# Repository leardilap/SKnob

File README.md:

# SKnob
The safety knob for your stove

# Overall shape
- Two main PCBs with 24x17mm dimmentions joined with ~~flex PCB~~ 2 wires

# Battery
- CR1225 or similar with ~50mA could allow to be mounted in the top of one of the PCBs as the space is round in the middle
- Holder: Manufacturer Part Number 	BK-885-TR 

# Bluetooth-STM32
- Use the STM32WB55Cx chip 
- Workshop: https://www.youtube.com/watch?v=5Lp9cDBzG94&list=PLnMKNibPkDnGRfqUO1Q_-1nW-tOKfDQbc&index=1

# Antena
- Manufacturer 	PulseLarsen Antennas
Manufacturer Part Number 	W3008 

# Similar product
- https://burneralert.com/

# Commercial
- Don't be a SKnob, do you mean our safety knobs for our burnner?. this is how I protect my family everyday, no more sleepless nights, waking up at night just to check the stove. With SKnob I feel safe. Don't wait, be a hero today.

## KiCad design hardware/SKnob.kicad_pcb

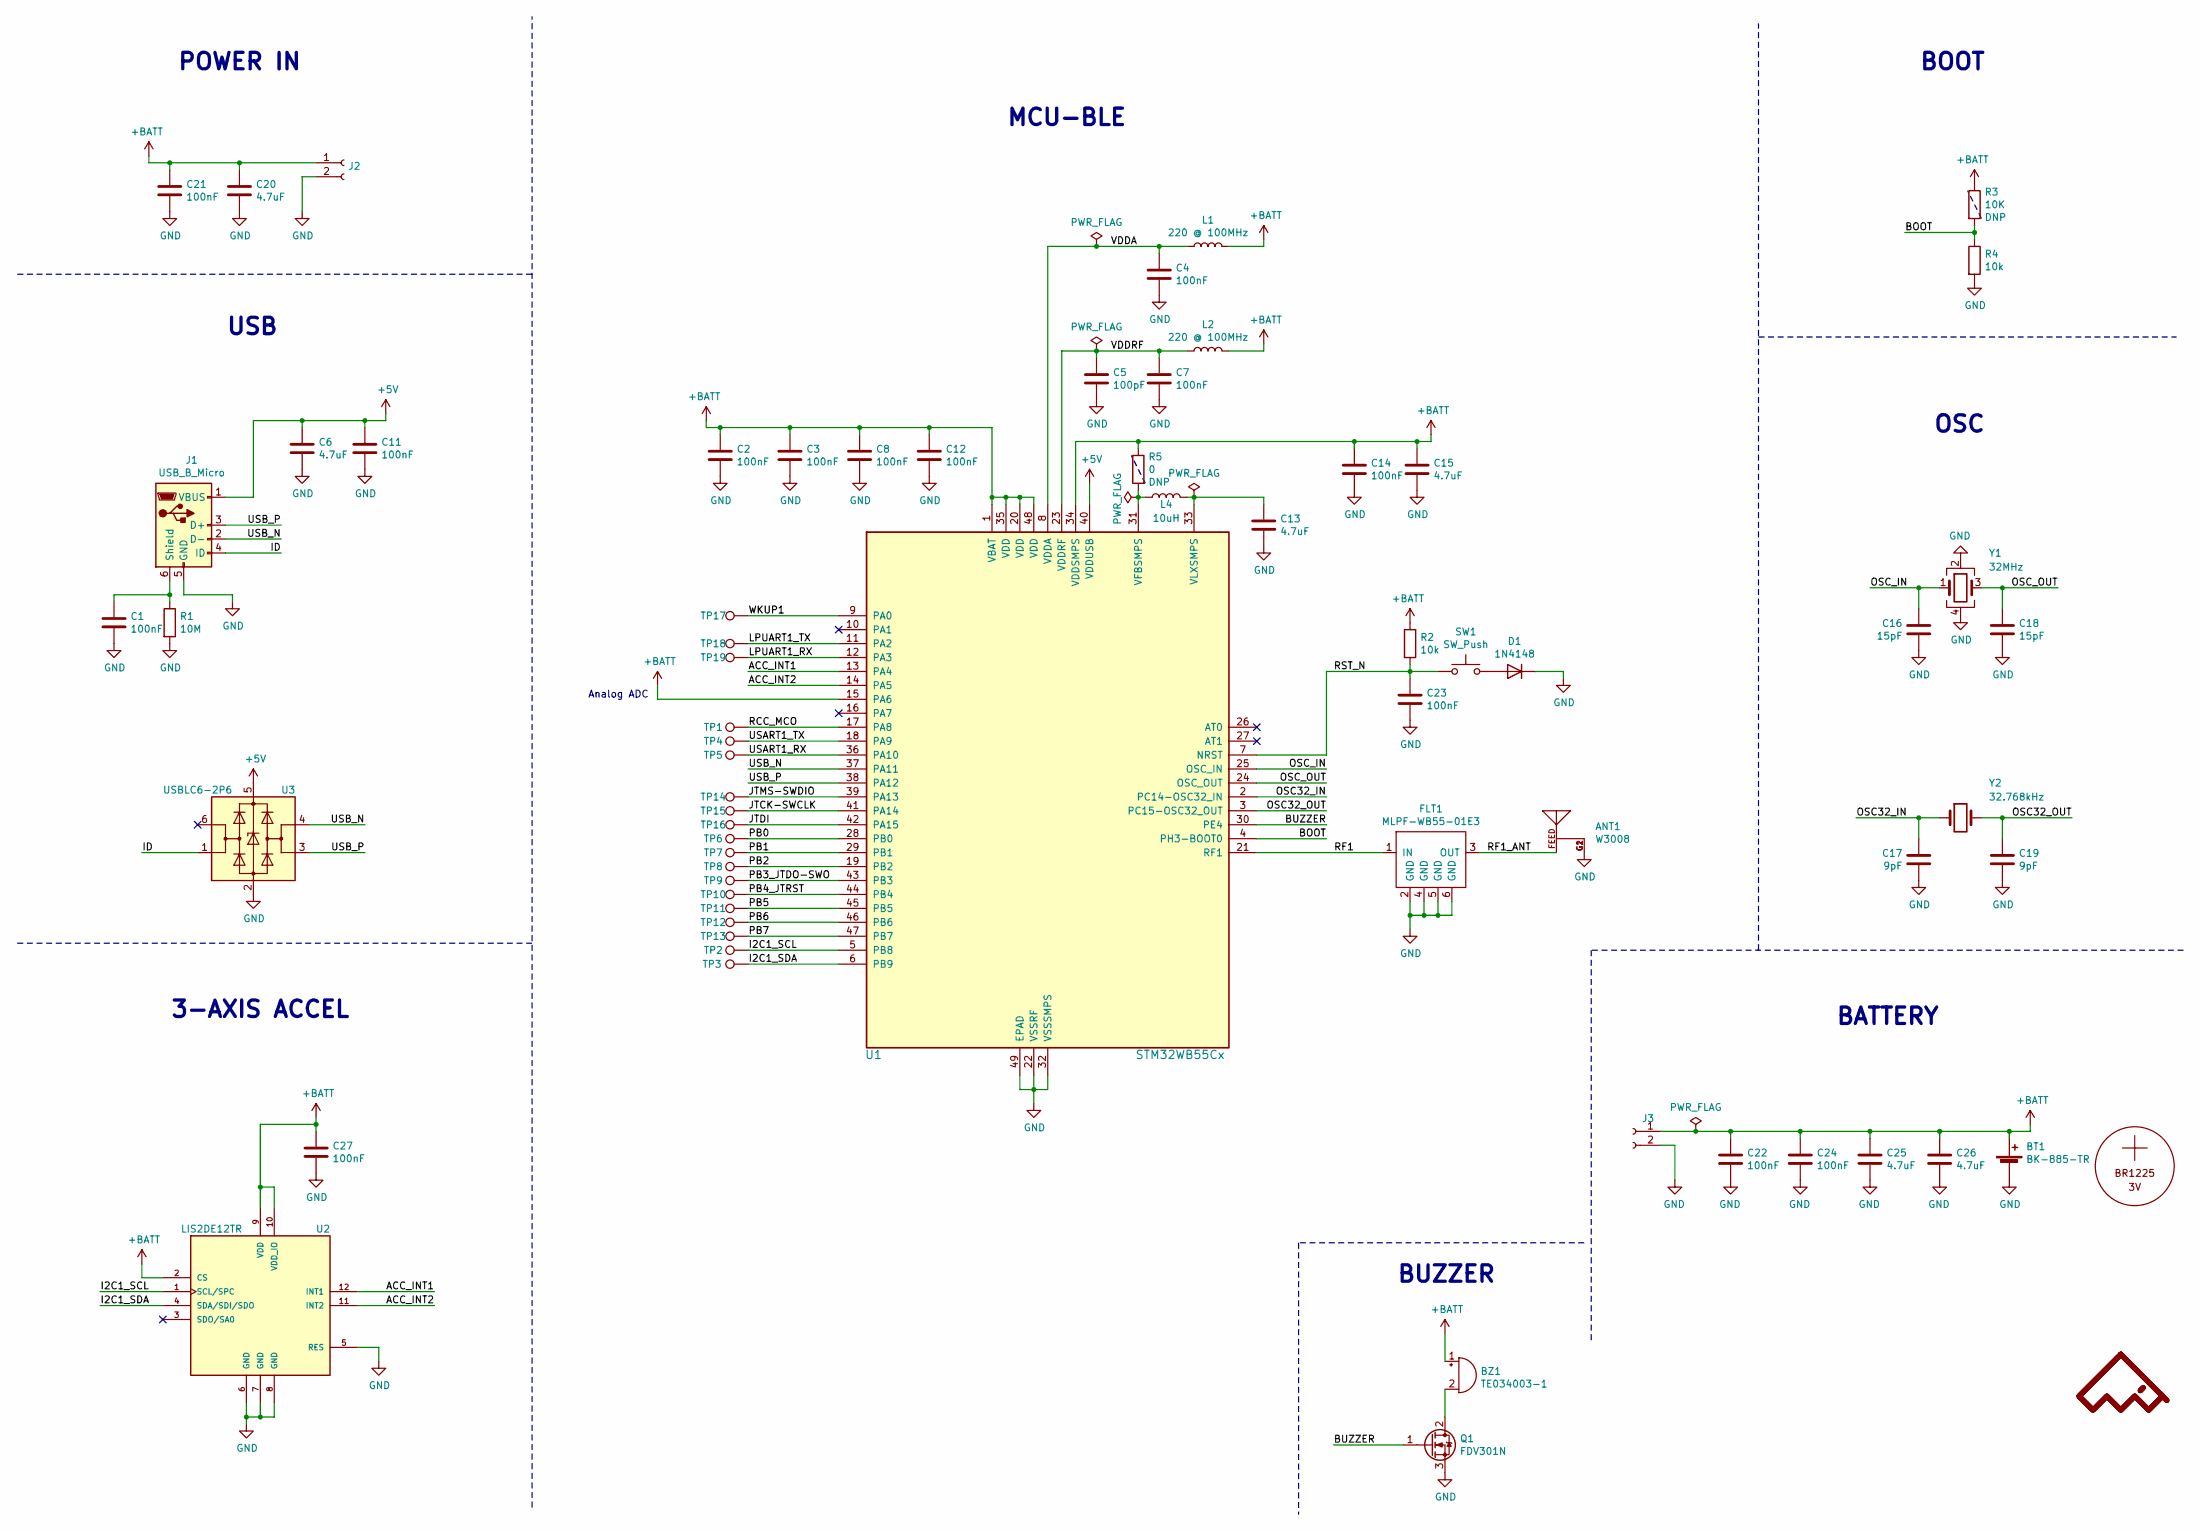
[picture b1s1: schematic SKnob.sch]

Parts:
ANT1: W3008; mouser# 673-W3008; digikey# 553-1530-1-ND
BATT1: BR1225; digikey# P183-ND
BT1: BK-885-TR; BatteryHolder_Keystone_3000_1x12mm; digikey# BK-885-CT-ND
BZ1: TE034003-1; digikey# 2104-TE034003-1CT-ND
C1, C2, C3, C4, C7, C8, C11, C12, C14, C21, C22, C23, C24, C27: 100nF; C_0402_1005Metric
C5: 100pF; C_0402_1005Metric
C6, C13, C15, C20, C25, C26: 4.7uF; C_0805_2012Metric
C16, C18: 15pF; C_0402_1005Metric
C17, C19: 9pF; C_0402_1005Metric
D1: 1N4148; D_0402_1005Metric; digikey# 1N4148WL2-TPMSCT-ND
FLT1: MLPF-WB55-01E3; mouser# 511-MLPF-WB55-01E3; digikey# 497-19088-1-ND
J1: USB_B_Micro; USB_Micro-B_Molex-105133-0001; mouser# 538-105133-0001; digikey# WM9734CT-ND
J2, J3: Conn_01x02; PinHeader_1x02_P2.00mm_Vertical; mouser# 855-M22-2510246; digikey# 952-2280-ND
L1, L2: 220 @ 100MHz; L_0603_1608Metric; mouser# 810-MPZ1608S221ATD25; digikey# 445-172893-1-ND
L4: 10uH; L_0603_1608Metric; mouser# 963-CBMF1608T100K; digikey# 587-1720-1-ND
Q1: FDV301N; SOT-23; mouser# 512-FDV301N; digikey# FDV301NCT-ND
R1: 10M; R_0402_1005Metric
R2, R4: 10k; R_0402_1005Metric
R3: 10K; R_0402_1005Metric_DNP
R5: 0; R_0402_1005Metric_DNP
SW1: SW_Push; SW_SPST_B3U-3000P; digikey# SW1022CT-ND
T1, T2: LA_LOGO
TP1, TP2, TP3, TP4, TP5, TP6, TP7, TP8, TP9, TP10, TP11, TP12, TP13, TP14, TP15, TP16, TP17, TP18, TP19: TestPoint; TestPoint_Pad_D1.0mm
U1: STM32WB55Cx; mouser# 511-STM32WB55CGU6; digikey# 497-18489-ND
U2: LIS2DE12TR; mouser# 511-LIS2DE12TR; digikey# 497-15997-1-ND
U3: USBLC6-2P6; SOT-666; mouser# 511-STEVAL-IPE023V1; digikey# 497-5026-1-ND
Y1: 32MHz; Crystal_SMD_2016-4Pin_2.0x1.6mm; mouser# 81-XRCGB32M000F1H02R; digikey# 490-18335-1-ND
Y2: 32.768kHz; Crystal_SMD_2012-2Pin_2.0x1.2mm; mouser# 520-.327-9-12R-C-T; digikey# XC2744CT-ND

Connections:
+5V: C6.1, C11.1, J1.1 (VBUS), U1.40 (VDDUSB), U3.5 (VBUS)
+BATT: BT1.1 (+), BZ1.1 (-), C2.1, C3.1, C8.1, C12.1, C14.1, C15.1, C20.1, C21.1, C22.1, C24.1, C25.1, C26.1, C27.1, J2.1, J3.1, L1.2, L2.2, R2.1, R3.1, R5.1, U1.1 (VBAT), U1.15 (PA6), U1.20 (VDD), U1.34 (VDDSMPS), U1.35 (VDD), U1.48 (VDD), U2.2 (CS), U2.9 (VDD), U2.10 (VDD_IO)
/ACC_INT1: U1.13 (PA4), U2.12 (INT1)
/ACC_INT2: U1.14 (PA5), U2.11 (INT2)
/BOOT: R3.2, R4.1, U1.4 (PH3-BOOT0)
/BUZZER: Q1.1 (G), U1.30 (PE4)
/I2C1_SCL: TP2.1, U1.5 (PB8), U2.1 (SCL/SPC)
/I2C1_SDA: TP3.1, U1.6 (PB9), U2.4 (SDA/SDI/SDO)
/ID: J1.4 (ID), U3.1 (I/O1)
/JTCK-SWCLK: TP15.1, U1.41 (PA14)
/JTDI: TP16.1, U1.42 (PA15)
/JTMS-SWDIO: TP14.1, U1.39 (PA13)
/LPUART1_RX: TP19.1, U1.12 (PA3)
/LPUART1_TX: TP18.1, U1.11 (PA2)
/OSC32_IN: C17.1, U1.2 (PC14-OSC32_IN), Y2.1
/OSC32_OUT: C19.1, U1.3 (PC15-OSC32_OUT), Y2.2
/OSC_IN: C16.1, U1.25 (OSC_IN), Y1.1
/OSC_OUT: C18.1, U1.24 (OSC_OUT), Y1.3
/PB0: TP6.1, U1.28 (PB0)
/PB1: TP7.1, U1.29 (PB1)
/PB2: TP8.1, U1.19 (PB2)
/PB3_JTDO-SWO: TP9.1, U1.43 (PB3)
/PB4_JTRST: TP10.1, U1.44 (PB4)
/PB5: TP11.1, U1.45 (PB5)
/PB6: TP12.1, U1.46 (PB6)
/PB7: TP13.1, U1.47 (PB7)
/RCC_MCO: TP1.1, U1.17 (PA8)
/RF1: FLT1.1 (IN), U1.21 (RF1)
/RF1_ANT: ANT1.FEED, FLT1.3 (OUT)
/RST_N: C23.1, R2.2, SW1.1, U1.7 (NRST)
/USART1_RX: TP5.1, U1.36 (PA10)
/USART1_TX: TP4.1, U1.18 (PA9)
/USB_N: J1.2 (D-), U1.37 (PA11), U3.4 (I/O2)
/USB_P: J1.3 (D+), U1.38 (PA12), U3.3 (I/O2)
/VDDA: C4.1, L1.1, U1.8 (VDDA)
/VDDRF: C5.1, C7.1, L2.1, U1.23 (VDDRF)
/WKUP1: TP17.1, U1.9 (PA0)
GND: ANT1.G1 (GND), ANT1.G2 (GND), BT1.2 (-), C1.2, C2.2, C3.2, C4.2, C5.2, C6.2, C7.2, C8.2, C11.2, C12.2, C13.2, C14.2, C15.2, C16.2, C17.2, C18.2, C19.2, C20.2, C21.2, C22.2, C23.2, C24.2, C25.2, C26.2, C27.2, D1.1 (K), FLT1.2 (GND), FLT1.4 (GND), FLT1.5 (GND), FLT1.6 (GND), J1.5 (GND), J2.2, J3.2, Q1.3 (S), R1.2, R4.2, U1.22 (VSSRF), U1.32 (VSSSMPS), U1.49 (EPAD), U2.5 (RES), U2.6 (GND), U2.7 (GND), U2.8 (GND), U3.2 (GND), Y1.2, Y1.4
unnamed: BZ1.2 (+), Q1.2 (D)
unnamed: C1.1, J1.6 (Shield), R1.1
unnamed: C13.1, L4.2, U1.33 (VLXSMPS)
unnamed: D1.2 (A), SW1.2
unnamed: L4.1, R5.2, U1.31 (VFBSMPS)

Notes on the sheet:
Analog ADC
BATTERY
OSC
BOOT
MCU-BLE
POWER IN
USB
3-AXIS ACCEL
BUZZER

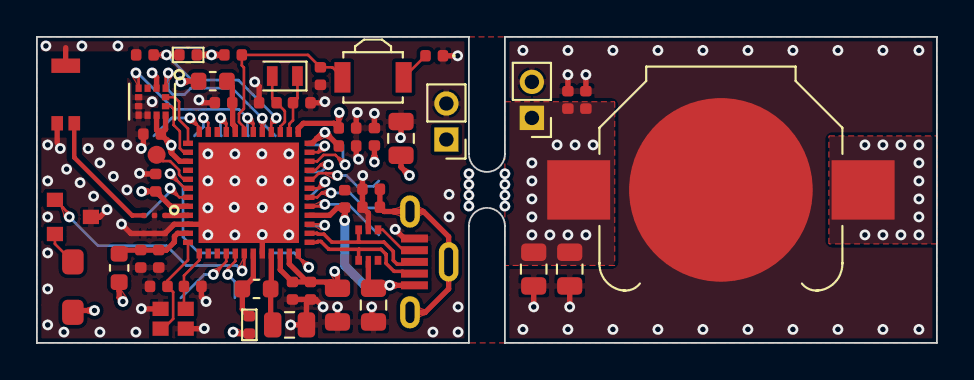
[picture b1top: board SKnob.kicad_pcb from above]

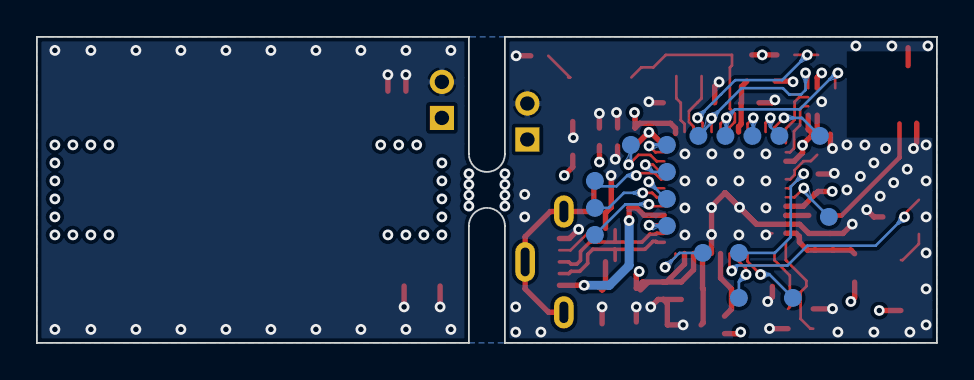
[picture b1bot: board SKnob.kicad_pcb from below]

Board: 4 copper layers, 50.0 x 17.0 mm, 71 parts (20 on the bottom side), 43 nets.

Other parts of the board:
QR*****: bozica.co

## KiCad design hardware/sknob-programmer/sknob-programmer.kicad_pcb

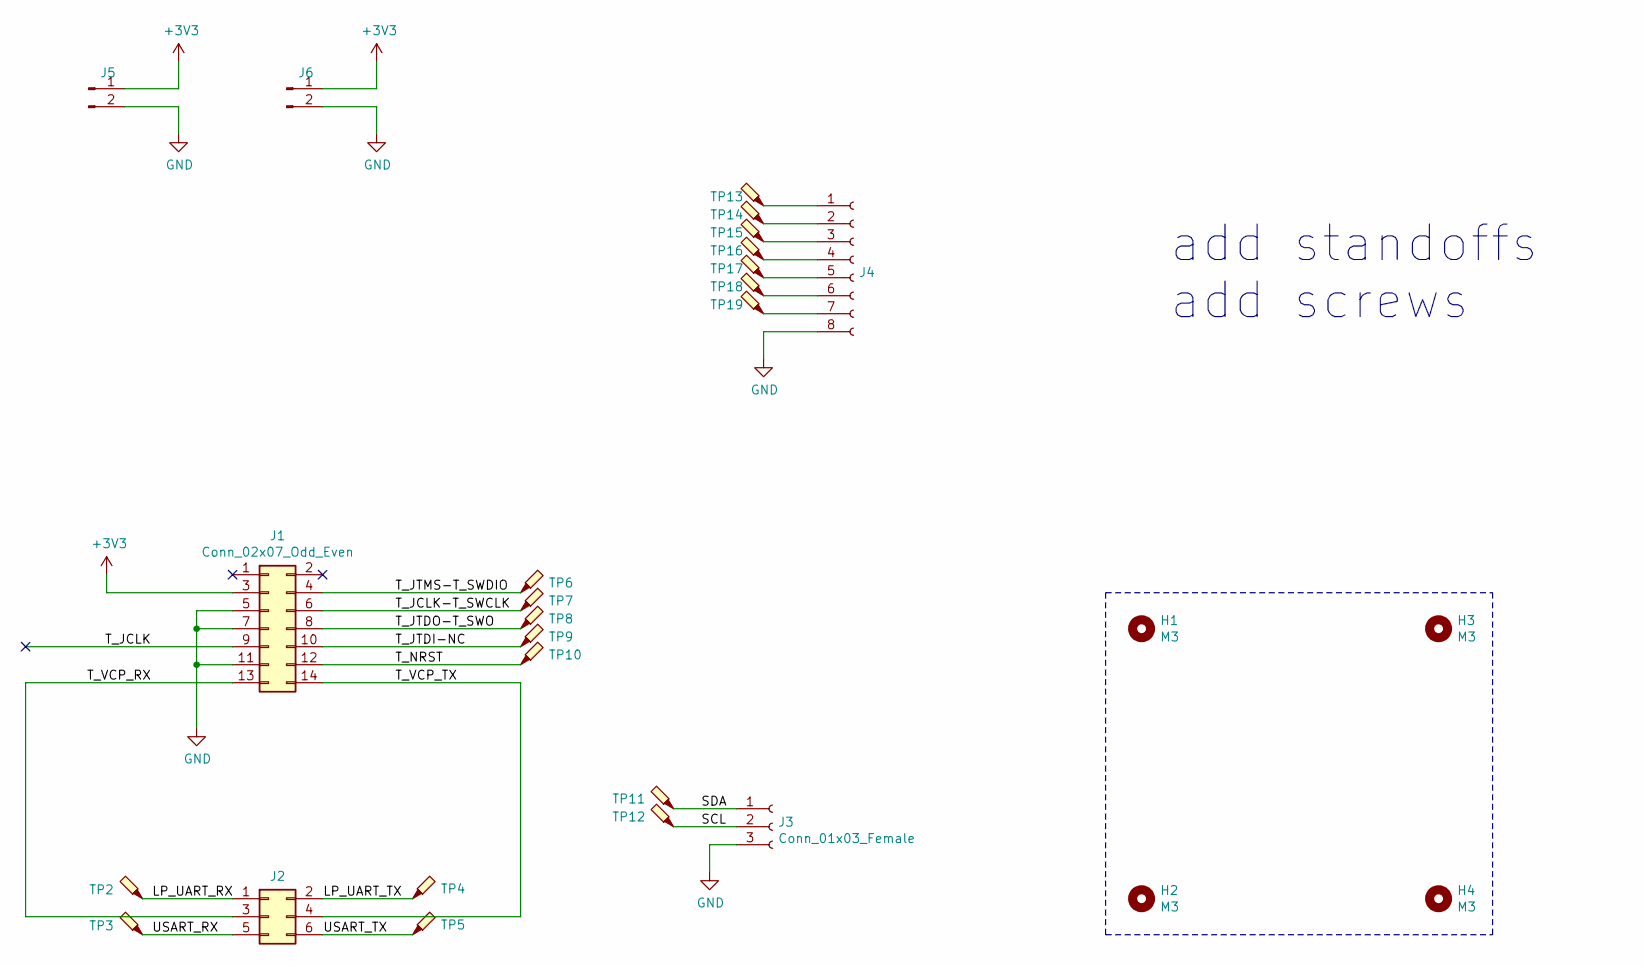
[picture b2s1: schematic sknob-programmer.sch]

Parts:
H1, H2, H3, H4: M3; MountingHole_3.2mm_M3
J1: Conn_02x07_Odd_Even; PinHeader_2x07_P1.27mm_Vertical
J2: Conn_02x03_Odd_Even; PinHeader_2x03_P2.54mm_Vertical
J3: Conn_01x03_Female; PinHeader_1x03_P2.54mm_Vertical
J4: Conn_01x08_Female; PinSocket_1x08_P2.54mm_Vertical
J5, J6: Conn_01x02_Male; PinHeader_1x02_P2.00mm_Vertical
TP2, TP3, TP4, TP5, TP6, TP7, TP8, TP9, TP10, TP11, TP12, TP13, TP14, TP15, TP16, TP17, TP18, TP19: P13-0123‎; PinHeader_1x01_P1.00mm_Vertical

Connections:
+3V3: J1.3, J5.1, J6.1
/LP_UART_RX: J2.1, TP2.1
/LP_UART_TX: J2.2, TP4.1
/SCL: J3.2, TP12.1
/SDA: J3.1, TP11.1
/T_JCLK-T_SWCLK: J1.6, TP7.1
/T_JTDI-NC: J1.10, TP9.1
/T_JTDO-T_SWO: J1.8, TP8.1
/T_JTMS-T_SWDIO: J1.4, TP6.1
/T_NRST: J1.12, TP10.1
/T_VCP_RX: J1.13, J2.3
/T_VCP_TX: J1.14, J2.4
/USART_RX: J2.5, TP3.1
/USART_TX: J2.6, TP5.1
GND: J1.5, J1.7, J1.11, J3.3, J4.8, J5.2, J6.2
unnamed: J4.1, TP13.1
unnamed: J4.2, TP14.1
unnamed: J4.3, TP15.1
unnamed: J4.4, TP16.1
unnamed: J4.5, TP17.1
unnamed: J4.6, TP18.1
unnamed: J4.7, TP19.1

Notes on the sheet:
add standoffs add screws

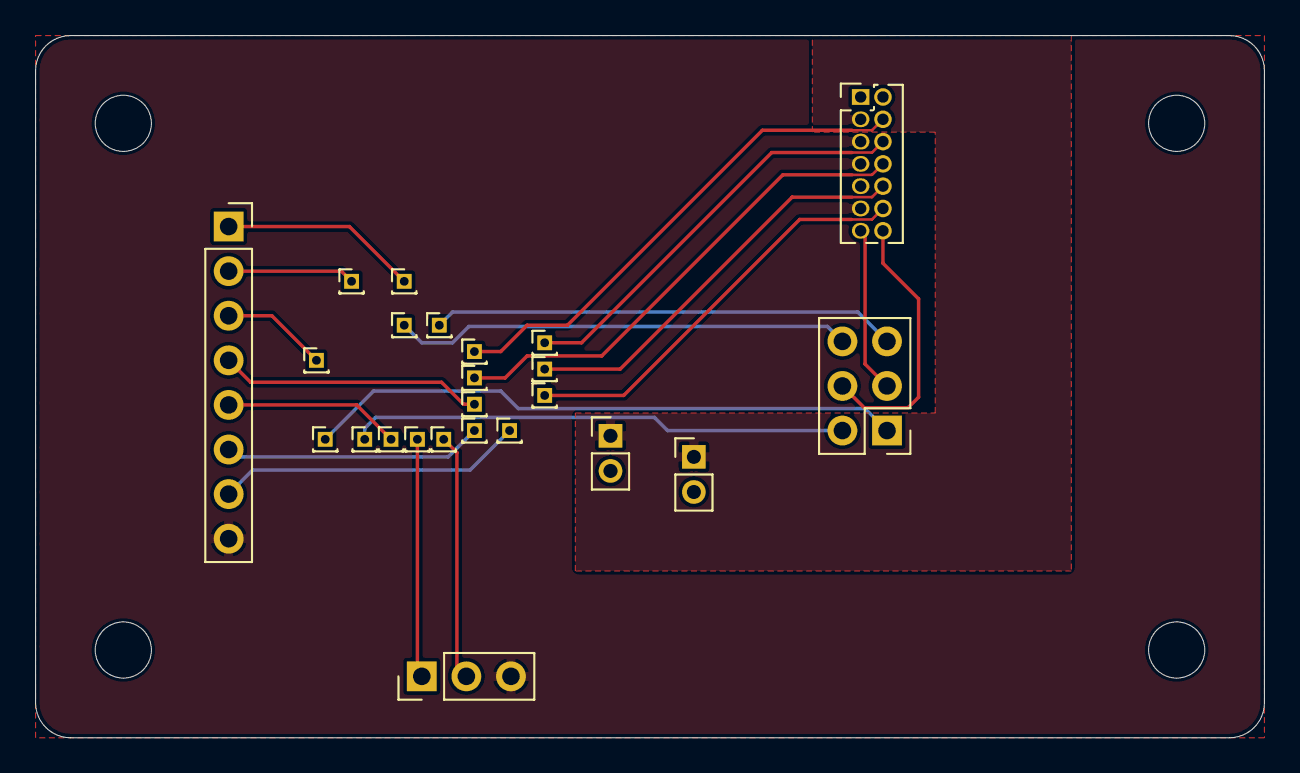
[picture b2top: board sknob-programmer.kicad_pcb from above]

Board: 4 copper layers, 70.0 x 40.0 mm, 29 parts (1 on the bottom side), 22 nets.

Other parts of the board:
QR*****: bozica.co

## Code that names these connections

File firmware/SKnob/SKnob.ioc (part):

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Mcu.UserName=STM32WB55CCUx
PA12.GPIOParameters=GPIO_Label
PA11.GPIOParameters=GPIO_Label
PA11.Mode=Device
PA6.GPIO_Label=ADC1_IN11_VBATT
RCC.SYSCLKSource=RCC_SYSCLKSOURCE_PLLCLK
PA12.Signal=USB_DP
PE4.GPIOParameters=GPIO_Label
RCC.HSE_VALUE=32000000
PB3.Mode=JTAG_5_pins
PA15.Mode=JTAG_5_pins
PB4.Mode=JTAG_5_pins
PC14-OSC32_IN.Mode=LSE-External-Oscillator
PA14.Mode=JTAG_5_pins
PA0.Mode=SYS_WakeUp0
PE4.GPIO_Label=BUZZER
PA8.Signal=RCC_MCO
PE4.Signal=GPIO_Output
PA0.Signal=SYS_WKUP1
PB9.Signal=I2C1_SDA
Mcu.Package=UFQFPN48
PA6.Signal=ADCx_IN11
PA10.Signal=USART1_RX
PA15.Signal=SYS_JTDI
PA5.GPIOParameters=GPIO_Label
PA4.GPIO_Label=ACCEL_INT1
PB4.Signal=SYS_JTRST
PA3.Signal=LPUART1_RX
PA6.GPIOParameters=GPIO_Label
PC15-OSC32_OUT.Mode=LSE-External-Oscillator
PA10.Mode=Asynchronous
PA11.GPIO_Label=USB_N
PC14-OSC32_IN.Signal=RCC_OSC32_IN
PA12.GPIO_Label=USB_P
PA13.Signal=SYS_JTMS-SWDIO
PA3.Mode=Asynchronous
PA9.Mode=Asynchronous
PB9.Mode=I2C
PA9.Signal=USART1_TX
PC15-OSC32_OUT.Signal=RCC_OSC32_OUT
PA5.Signal=GPIO_Input
board=custom
PA4.GPIOParameters=GPIO_Label
PA13.Mode=JTAG_5_pins
Mcu.Name=STM32WB55CCUx
PA2.Signal=LPUART1_TX
PB3.Signal=SYS_JTDO-SWO
PA4.Signal=GPIO_Input
RCC.SYSCLKFreq_VALUE=64000000
PA12.Mode=Device
PA5.GPIO_Label=ACCEL_INT2
PA11.Signal=USB_DM
PA14.Signal=SYS_JTCK-SWCLK
PB8.Mode=I2C
PB8.Signal=I2C1_SCL
PA2.Mode=Asynchronous
PA8.Mode=Clock-out

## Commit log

2020-05-20 init commit, add readme
2020-05-20 similar product
2020-05-20 commercial
2020-05-20 minor fix
2020-05-20 draft with dimmentions of PCB@
2020-05-21 layout guide
2020-05-24 antena section
2020-05-25 rf network
2020-06-01 stm32wb chip selection
2020-06-01 preliminary routing
2020-06-04 added accel
2020-08-02 update hardware to include test points in the back and commit auto generated firmware project files
2020-08-02 finishing touches
2020-08-02 added buzzer to PE4
2020-08-02 hardware Rev 1.0
2020-08-02 autogen firmware files using cubeide
2020-08-02 Tag: Rev 1.0
2020-08-02 remove silk from footprints, replace silk gerber with empty manually
2020-08-02 shopping carts from digikey and mouser, added mouser part numbers to sch
2020-10-15 added programmer project
2020-10-15 3D holder model for programmer
2020-12-18 pdf bom version
